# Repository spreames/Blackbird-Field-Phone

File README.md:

# Blackbird Field Phone

A cave rescue field phone for replacing the TP-6N.

#### **Status: Incomplete -- do not for design use until all files loaded**

### Background:

In the USA, cave rescue communications have been done with military field phones for decades. These are two-wire systems that are part of a party-line system (aka parallel connected). The National Cave Rescue Commission (NCRC) has a cache of these phones that are used for training. These units are available in the military surplus stores and online such as eBay. Over the years these field phones have become standard for all cave rescue teams in the USA.

There are three standard field phones that are in use today. The TA-1 ("sound powered" phone) which does not requires batteries but has a very limited range of 2 miles or less. The TA-312 (the "crank phone") has a theoretical range of 20 miles but weights 10.0 lbs with batteries! The TP-6N (the "NATO phone") has the same range but has solid-state circuitry, is much lighter (2.5 lbs), and much smaller.

The problem is that the units are failing. There a no replacement parts, no schematics, and no theory of operation. The most recent model, the TP-6N, was designed in 1973 -- a 50-year old design!

### Introduction to the Blackbird:

In December 2021, the NCRC formed the Communication Committee (CommComm) to address the increasing failure rate with the military phones in the field. The group decided to begin the design of a clone of the TP-6N which was named "Blackbird". Many of the original components are obsolete and very hard to obtain such as custom transformers and uni-junction transistors. So the team designed a functional clone such that works the same as the TP-6N but uses the modern techniques such as SMT components, KiCAD schematics and PCB layouts, 3D printing, and LTspice simulations.

The requirements and goals are:

- Backward compatable with the existing field phones

- Lighter, smaller, and requiring less power

- Runs off three AA batteries

- Is the same cost or less as TP-6Ns on eBay (when they are available)

The complete Goals and Requirements document is 13 pages and is linked here:

xxxxxx

### Block Diagram:

xxxx

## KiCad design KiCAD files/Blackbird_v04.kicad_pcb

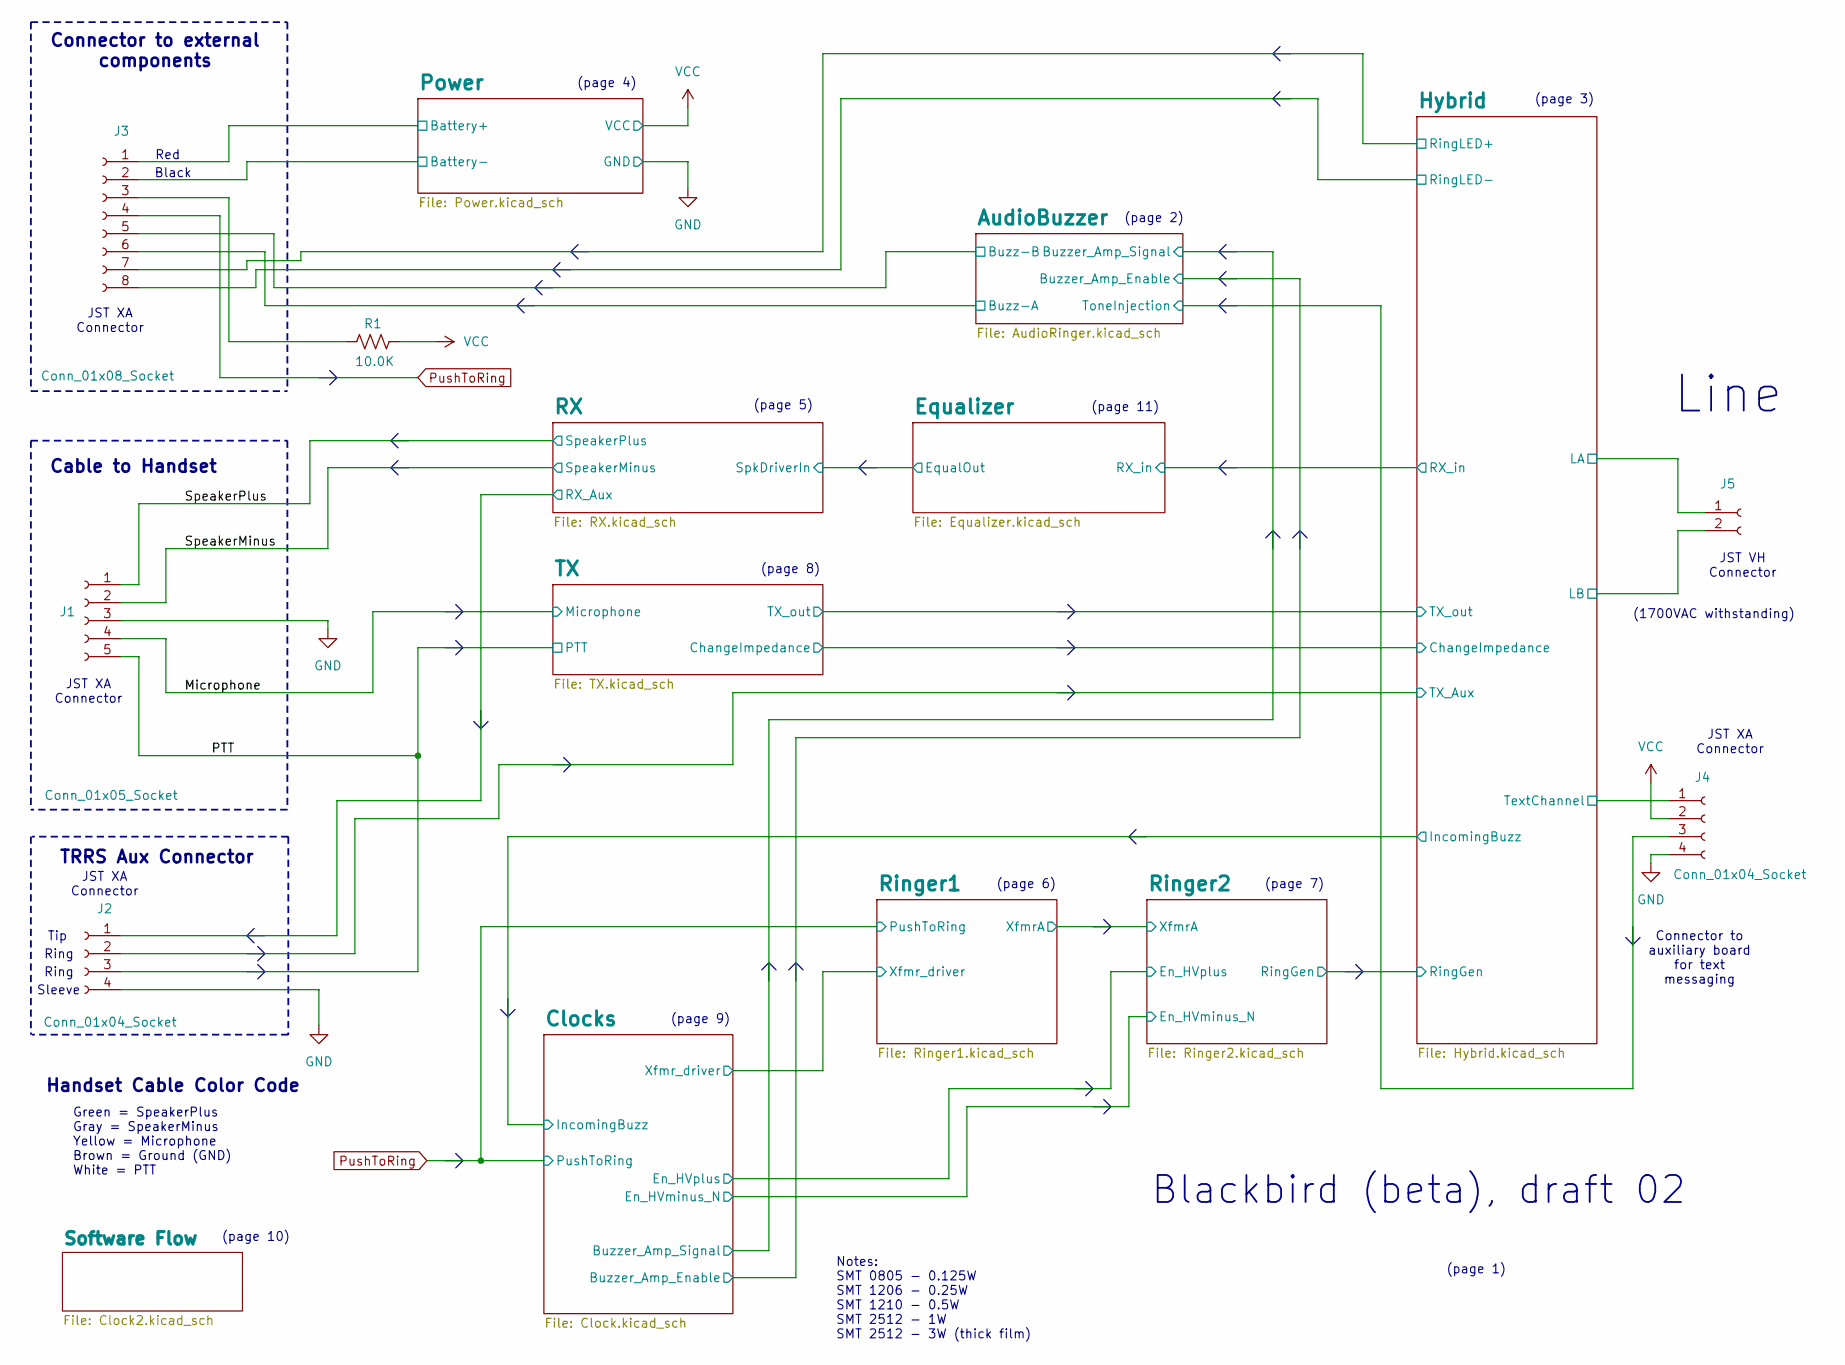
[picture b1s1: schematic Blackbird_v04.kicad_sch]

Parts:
J1: Conn_01x05_Socket; JST_XA_S05B-XASK-1_1x05_P2.50mm_Horizontal_w_housing
J2, J4: Conn_01x04_Socket; JST_XA_S04B-XASK-1_1x04_P2.50mm_Horizontal_w_housing
J3: Conn_01x08_Socket; JST_XA_S08B-XASK-1_1x08_P2.50mm_Horizontal_w_housing
J5: Conn_01x02_Socket; JST_VH_S2P-VH_1x02_P3.96mm_Horizontal_w_housing
R1: 10.0K; R_0805_2012Metric_Pad1.20x1.40mm_HandSolder

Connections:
/AudioBuzzer/Buzz-A: J3.6; also elsewhere on the board
/AudioBuzzer/Buzz-B: J3.5; also elsewhere on the board
/AudioBuzzer/ToneInjection: J4.3; also elsewhere on the board
/Hybrid/LA: J5.1; also elsewhere on the board
/Hybrid/LB: J5.2; also elsewhere on the board
/Hybrid/RingLED+: J3.7; also elsewhere on the board
/Hybrid/RingLED-: J3.8; also elsewhere on the board
/Hybrid/TX_Aux: J2.2; also elsewhere on the board
/Hybrid/TextChannel: J4.1; also elsewhere on the board
/Microphone: J1.4; also elsewhere on the board
/PTT: J1.5, J2.3; also elsewhere on the board
/Power/Battery+: J3.1; also elsewhere on the board
/Power/Battery-: J3.2; also elsewhere on the board
/RX/RX_Aux: J2.1; also elsewhere on the board
/SpeakerMinus: J1.2; also elsewhere on the board
/SpeakerPlus: J1.1; also elsewhere on the board
GND: J1.3, J2.4, J4.4; also elsewhere on the board
unnamed: J3.3, R1.1
PushToRing: J3.4; also elsewhere on the board
VCC: J4.2, R1.2; also elsewhere on the board

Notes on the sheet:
(page 4)
(page 10)
(page 5)
JST XA Connector
(1700VAC withstanding)
Tip
Cable to Handset
Sleeve
JST VH Connector
(page 8)
Green = SpeakerPlus Gray = SpeakerMinus Yellow = Microphone Brown = Ground (GND) White = PTT
(page 7)
Connector to auxiliary board for text messaging
Notes: SMT 0805 - 0.125W SMT 1206 - 0.25W SMT 1210 - 0.5W SMT 2512 - 1W SMT 2512 - 3W (thick film)
(page 11)
(page 9)
(page 1)
Ring
Red
TRRS Aux Connector
Black
(page 2)
Handset Cable Color Code
Connector to external components
(page 3)
Line
(page 6)
Blackbird (beta), draft 02

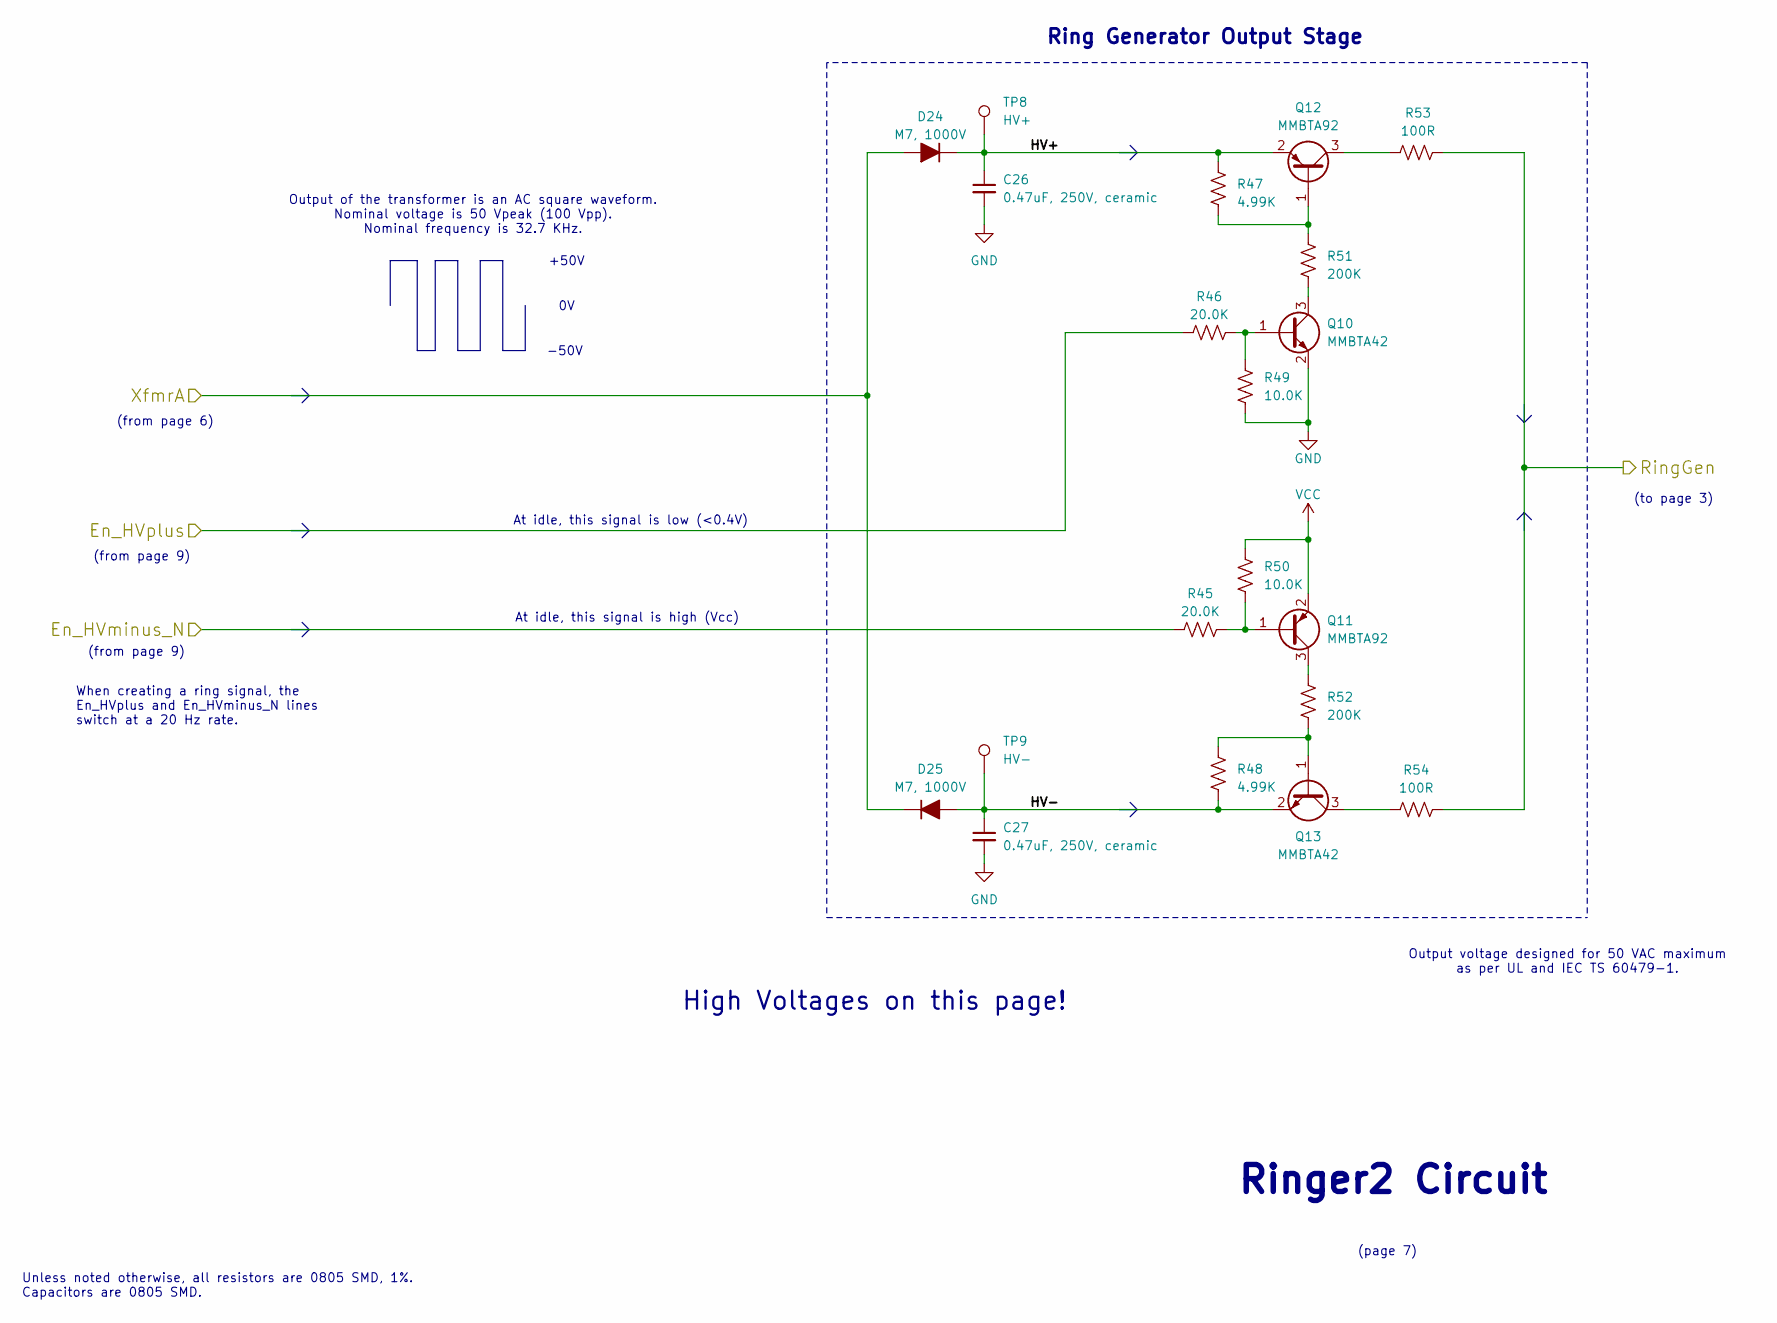
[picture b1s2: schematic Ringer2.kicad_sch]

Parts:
C26, C27: 0.47uF, 250V, ceramic; C_1812_4532Metric_Pad1.57x3.40mm_HandSolder
D24, D25: M7, 1000V; D_SMA_Handsoldering
Q10, Q13: MMBTA42; SOT-23_Handsoldering
Q11, Q12: MMBTA92; SOT-23_Handsoldering
R45, R46: 20.0K; R_0805_2012Metric_Pad1.20x1.40mm_HandSolder
R47, R48: 4.99K; R_0805_2012Metric_Pad1.20x1.40mm_HandSolder
R49, R50: 10.0K; R_0805_2012Metric_Pad1.20x1.40mm_HandSolder
R51, R52: 200K; R_0805_2012Metric_Pad1.20x1.40mm_HandSolder
R53, R54: 100R; R_1210_3225Metric_Pad1.30x2.65mm_HandSolder
TP8: HV+; Test_point_47mil_scope_probe
TP9: HV-; Test_point_47mil_scope_probe

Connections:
/Clocks/En_HVminus_N: R45.1; also elsewhere on the board
/Clocks/En_HVplus: R46.1; also elsewhere on the board
/Hybrid/RingGen: R53.2, R54.2; also elsewhere on the board
/Ringer1/XfmrA: D24.2 (A), D25.1 (K); also elsewhere on the board
/Ringer2/HV+: C26.1, D24.1 (K), Q12.2 (E), R47.1, TP8.1
/Ringer2/HV-: C27.1, D25.2 (A), Q13.2 (E), R48.2, TP9.1
GND: C26.2, C27.2, Q10.2 (E), R49.1; also elsewhere on the board
unnamed: Q10.1 (B), R46.2, R49.2
unnamed: Q10.3 (C), R51.2
unnamed: Q11.1 (B), R45.2, R50.1
unnamed: Q11.3 (C), R52.1
unnamed: Q12.1 (B), R47.2, R51.1
unnamed: Q12.3 (C), R53.1
unnamed: Q13.1 (B), R48.1, R52.2
unnamed: Q13.3 (C), R54.1
VCC: Q11.2 (E), R50.2; also elsewhere on the board

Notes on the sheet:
At idle, this signal is high (Vcc)
When creating a ring signal, the En_HVplus and En_HVminus_N lines switch at a 20 Hz rate.
(from page 6)
Ringer2 Circuit
(from page 9)
(to page 3)
Output of the transformer is an AC square waveform. Nominal voltage is 50 Vpeak (100 Vpp). Nominal frequency is 32.7 KHz.
Output voltage designed for 50 VAC maximum as per UL and IEC TS 60479-1.
Unless noted otherwise, all resistors are 0805 SMD, 1%. Capacitors are 0805 SMD.
+50V
-50V
Ring Generator Output Stage
At idle, this signal is low (<0.4V)
High Voltages on this page!
(page 7)

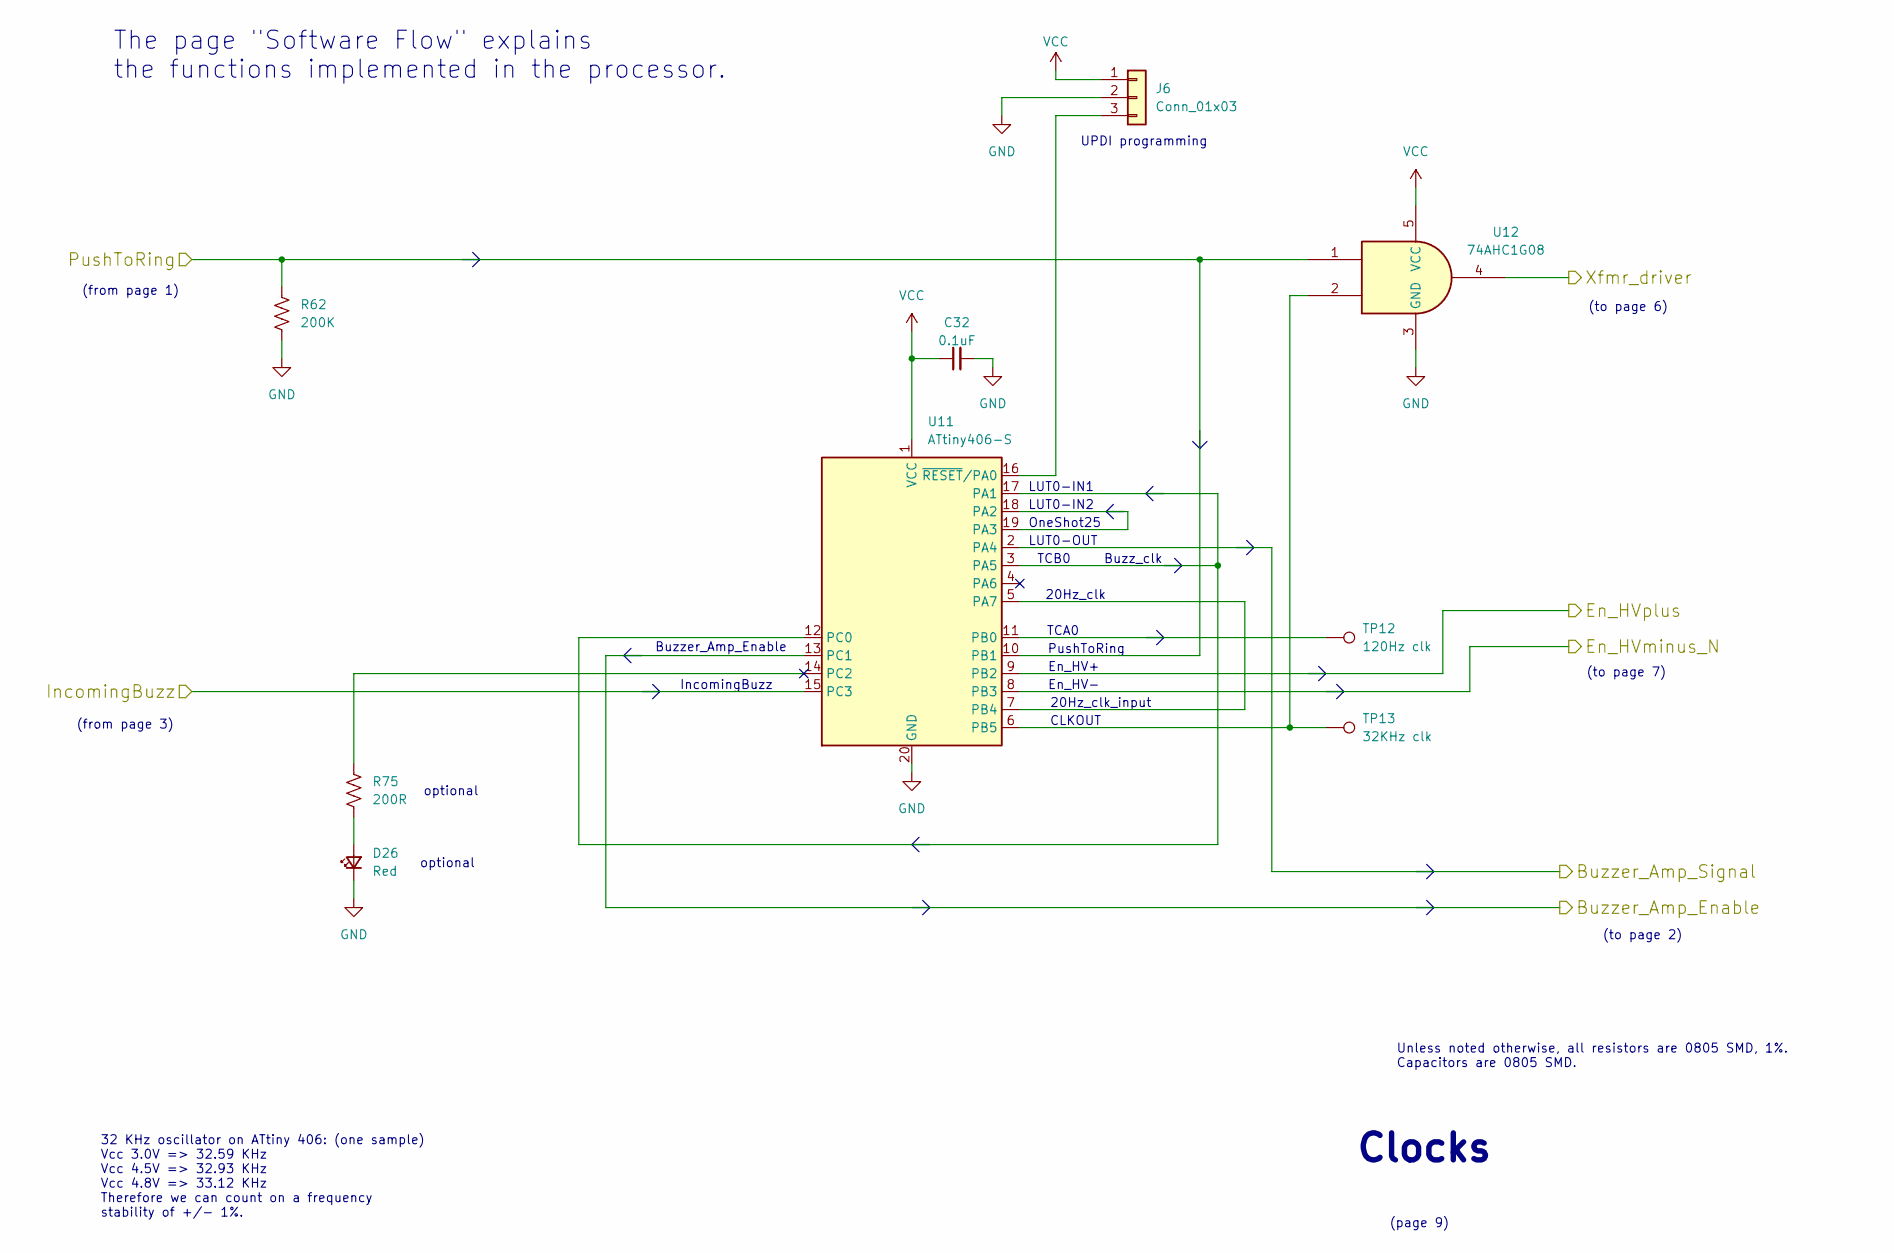
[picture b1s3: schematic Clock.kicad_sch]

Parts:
C32: 0.1uF; C_0805_2012Metric_Pad1.18x1.45mm_HandSolder
D26: Red; LED_1206_3216Metric_Red
J6: Conn_01x03; PinSocket_1x03_P2.54mm_Vertical
R62: 200K; R_0805_2012Metric_Pad1.20x1.40mm_HandSolder
R75: 200R; R_0805_2012Metric_Pad1.20x1.40mm_HandSolder
TP12: 120Hz clk; Test_point_47mil_scope_probe
TP13: 32KHz clk; Test_point_47mil_scope_probe
U11: ATtiny406-S; SOIC-20W_7.5x12.8mm_P1.27mm
U12: 74AHC1G08; SOT-23-5_HandSoldering

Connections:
/AudioBuzzer/Buzzer_Amp_Enable: U11.13 (PC1); also elsewhere on the board
/AudioBuzzer/Buzzer_Amp_Signal: U11.2 (PA4); also elsewhere on the board
/Clocks/En_HVminus_N: U11.8 (PB3); also elsewhere on the board
/Clocks/En_HVplus: U11.9 (PB2); also elsewhere on the board
/Clocks/IncomingBuzz: U11.15 (PC3); also elsewhere on the board
/Clocks/Xfmr_driver: U12.4; also elsewhere on the board
GND: C32.2, D26.1 (K), J6.2, R62.1, U11.20 (GND), U12.3 (GND); also elsewhere on the board
unnamed: D26.2 (A), R75.1
unnamed: J6.3, U11.16 (~RESET/PA0)
unnamed: U11.3 (PA5), U11.12 (PC0), U11.17 (PA1)
unnamed: U11.18 (PA2), U11.19 (PA3)
unnamed: U11.5 (PA7), U11.7 (PB4)
unnamed: TP12.1, U11.11 (PB0)
unnamed: TP13.1, U11.6 (PB5), U12.2
PushToRing: R62.2, U11.10 (PB1), U12.1; also elsewhere on the board
VCC: C32.1, J6.1, U11.1 (VCC), U12.5 (VCC); also elsewhere on the board

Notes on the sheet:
The page "Software Flow" explains the functions implemented in the processor.
LUT0-OUT
Clocks
Buzzer_Amp_Enable
(from page 1)
TCB0
IncomingBuzz
(page 9)
(to page 6)
LUT0-IN1
UPDI programming
OneShot25
En_HV+
20Hz_clk_input
optional
CLKOUT
(to page 2)
Unless noted otherwise, all resistors are 0805 SMD, 1%. Capacitors are 0805 SMD.
En_HV-
TCA0
LUT0-IN2
20Hz_clk
(from page 3)
PushToRing
32 KHz oscillator on ATtiny 406: (one sample) Vcc 3.0V => 32.59 KHz Vcc 4.5V => 32.93 KHz Vcc 4.8V => 33.12 KHz Therefore we can count on a frequency stability of +/- 1%.
(to page 7)
Buzz_clk

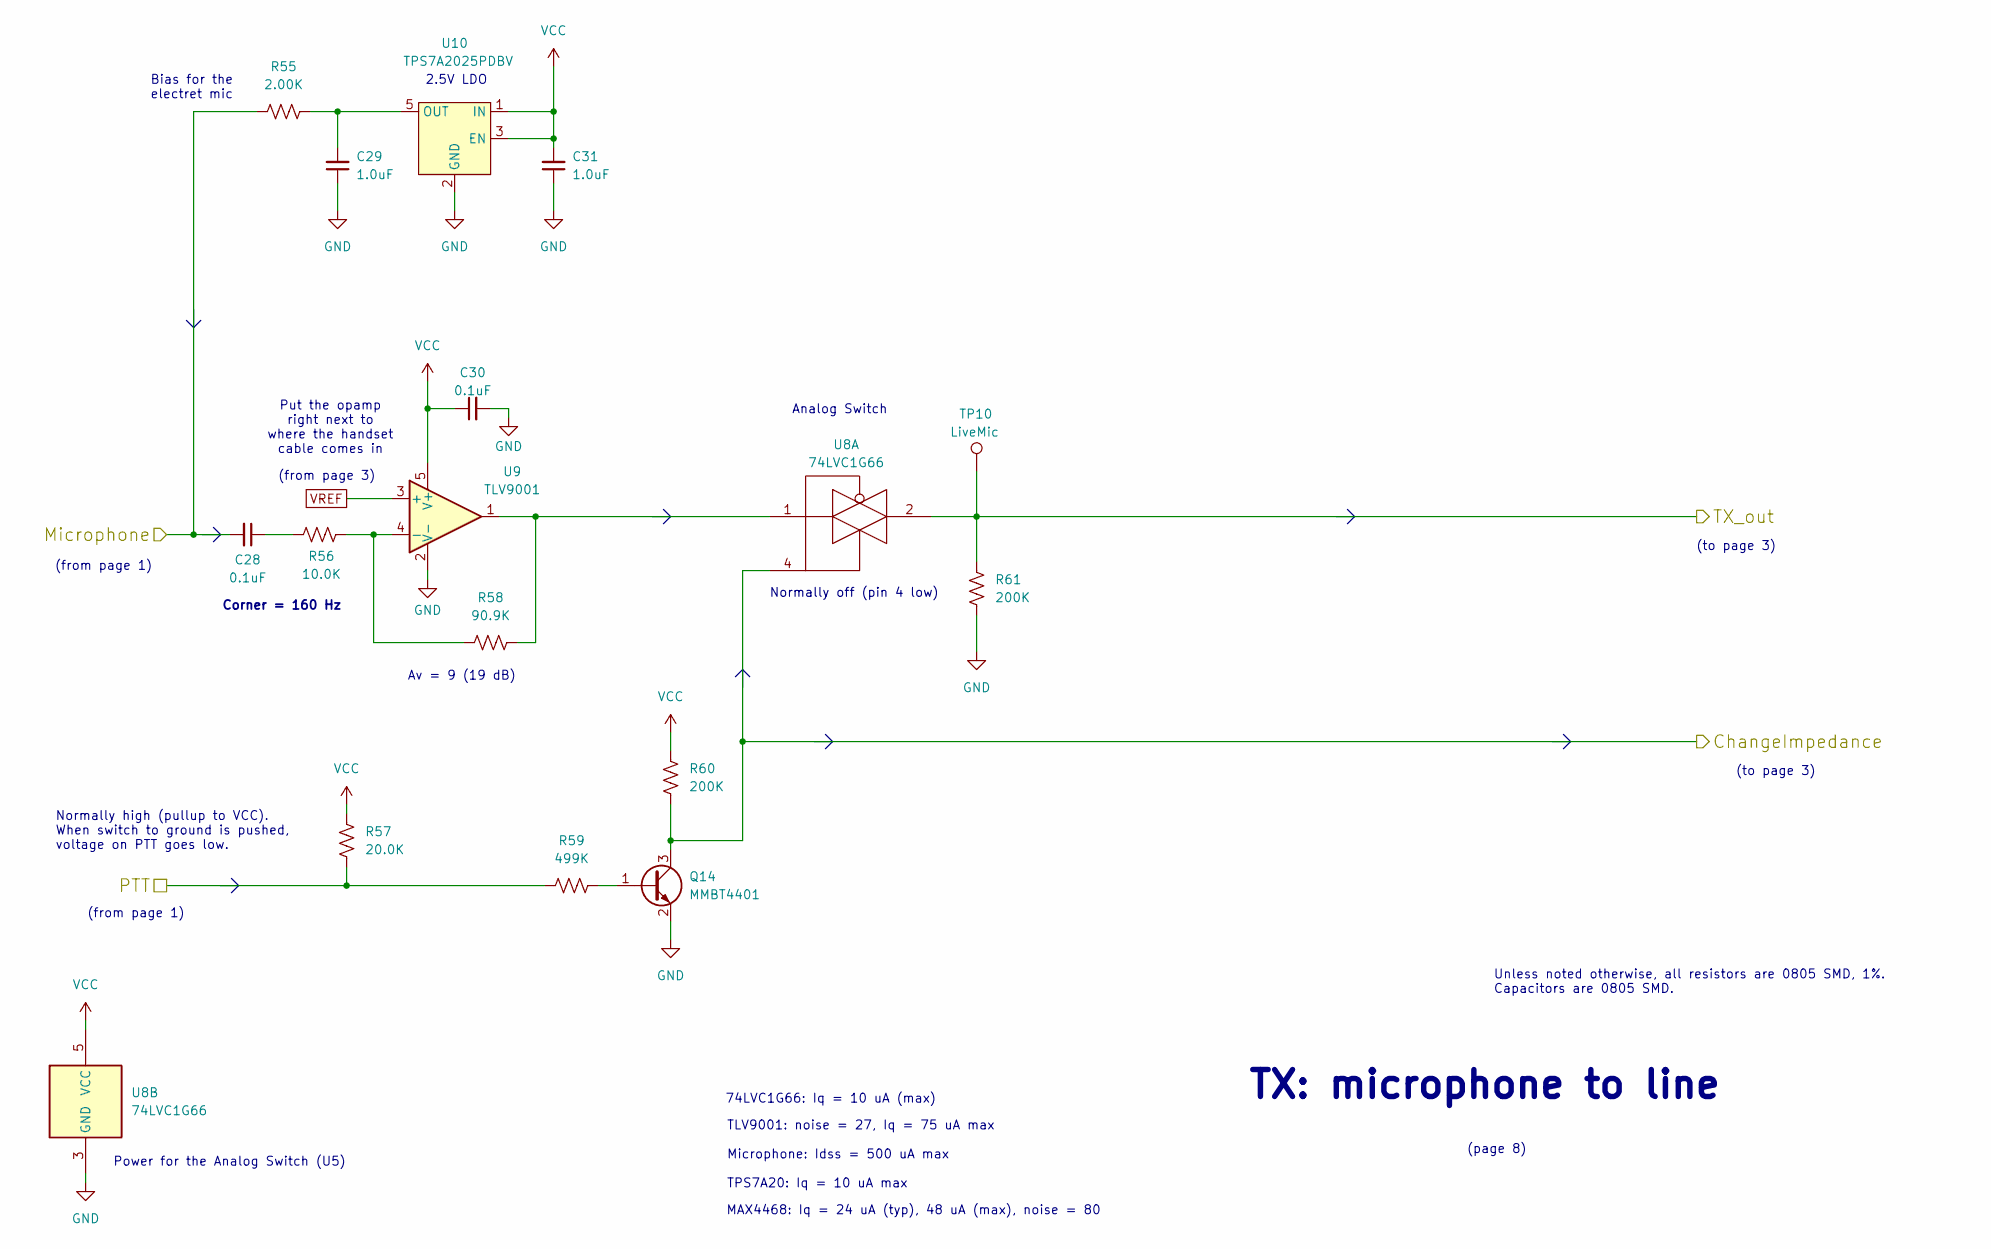
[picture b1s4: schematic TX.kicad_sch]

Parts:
C28, C30: 0.1uF; C_0805_2012Metric_Pad1.18x1.45mm_HandSolder
C29, C31: 1.0uF; C_0805_2012Metric_Pad1.18x1.45mm_HandSolder
Q14: MMBT4401; SOT-23_Handsoldering
R55: 2.00K; R_0805_2012Metric_Pad1.20x1.40mm_HandSolder
R56: 10.0K; R_0805_2012Metric_Pad1.20x1.40mm_HandSolder
R57: 20.0K; R_0805_2012Metric_Pad1.20x1.40mm_HandSolder
R58: 90.9K; R_0805_2012Metric_Pad1.20x1.40mm_HandSolder
R59: 499K; R_0805_2012Metric_Pad1.20x1.40mm_HandSolder
R60, R61: 200K; R_0805_2012Metric_Pad1.20x1.40mm_HandSolder
TP10: LiveMic; Test_point_47mil_scope_probe
U8: 74LVC1G66; SOT-23-5_HandSoldering
U9: TLV9001; SOT-23-5_HandSoldering
U10: TPS7A2025PDBV; SOT-23-5_HandSoldering

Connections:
/Hybrid/ChangeImpedance: Q14.3 (C), R60.1, U8.4; also elsewhere on the board
/Hybrid/TX_out: R61.1, TP10.1, U8.2; also elsewhere on the board
/Microphone: C28.2, R55.1; also elsewhere on the board
/PTT: R57.2, R59.1; also elsewhere on the board
GND: C29.1, C30.2, C31.1, Q14.2 (E), R61.2, U8.3 (GND), U9.2 (V-), U10.2 (GND); also elsewhere on the board
unnamed: C28.1, R56.1
unnamed: Q14.1 (B), R59.2
unnamed: R58.2, U8.1, U9.1
unnamed: R56.2, R58.1, U9.4 (-)
unnamed: C29.2, R55.2, U10.5 (OUT)
VCC: C30.1, C31.2, R57.1, R60.2, U8.5 (VCC), U9.5 (V+), U10.1 (IN), U10.3 (EN); also elsewhere on the board
VREF: U9.3 (+); also elsewhere on the board

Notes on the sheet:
Corner = 160 Hz
TLV9001: noise = 27, Iq = 75 uA max Microphone: Idss = 500 uA max TPS7A20: Iq = 10 uA max
(page 8)
(from page 1)
2.5V LDO
Av = 9 (19 dB)
Unless noted otherwise, all resistors are 0805 SMD, 1%. Capacitors are 0805 SMD.
Normally off (pin 4 low)
TX: microphone to line
Normally high (pullup to VCC). When switch to ground is pushed, voltage on PTT goes low.
Power for the Analog Switch (U5)
Analog Switch
(to page 3)
74LVC1G66: Iq = 10 uA (max)
(from page 3)
Bias for the electret mic
MAX4468: Iq = 24 uA (typ), 48 uA (max), noise = 80
Put the opamp right next to where the handset cable comes in

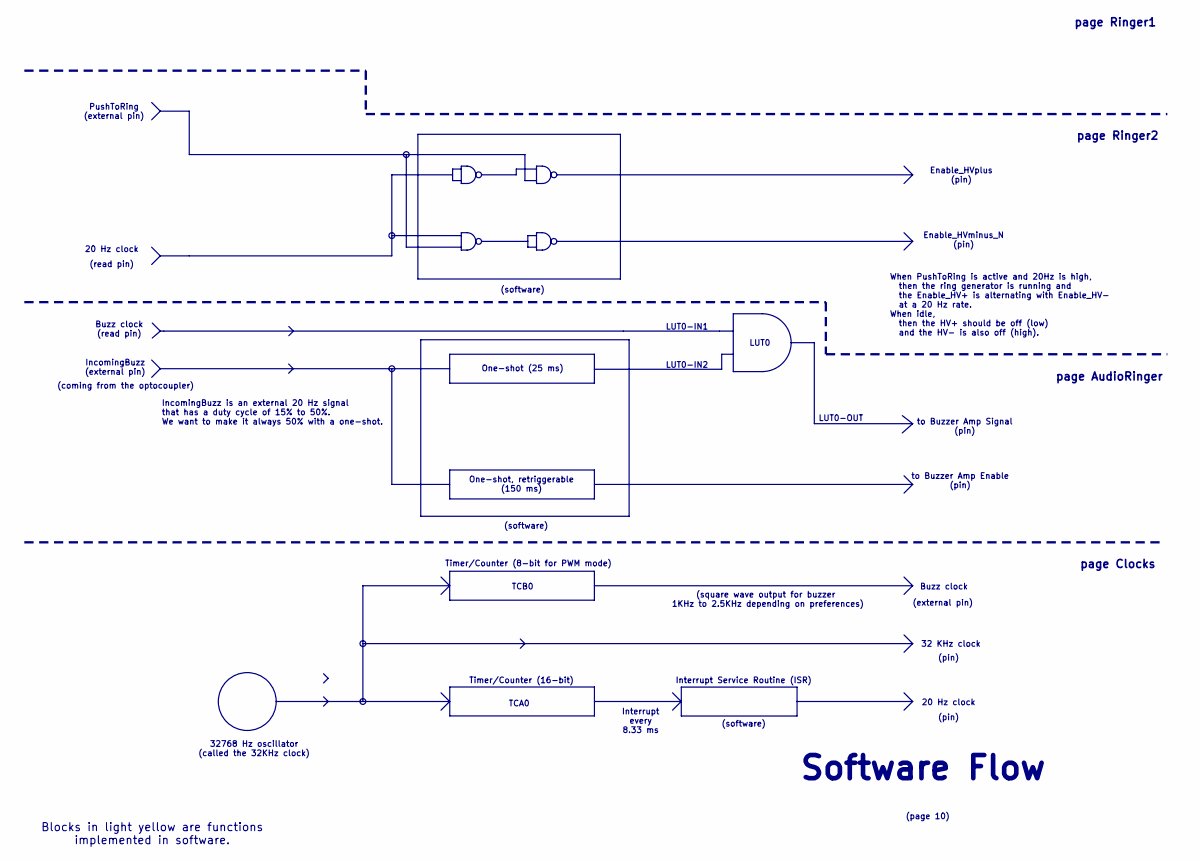
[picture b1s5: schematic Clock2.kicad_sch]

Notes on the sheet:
20 Hz clock
One-shot, retriggerable (150 ms)
Enable_HVminus_N (pin)
32 KHz clock
to Buzzer Amp Signal (pin)
Interrupt Service Routine (ISR)
Timer/Counter (8-bit for PWM mode)
(external pin)
(page 10)
LUT0-IN2
(pin)
Timer/Counter (16-bit)
Blocks in light yellow are functions implemented in software.
page Clocks
Enable_HVplus (pin)
(square wave output for buzzer 1KHz to 2.5KHz depending on preferences)
(software)
Software Flow
page Ringer1
32768 Hz oscillator (called the 32KHz clock)
LUT0-IN1
IncomingBuzz (external pin)
(read pin)
One-shot (25 ms)
PushToRing (external pin)
page AudioRinger
TCA0
page Ringer2
(coming from the optocoupler)
LUT0
IncomingBuzz is an external 20 Hz signal that has a duty cycle of 15% to 50%. We want to make it always 50% with a one-shot.
TCB0
LUT0-OUT
to Buzzer Amp Enable (pin)
Interrupt every 8.33 ms
Buzz clock (read pin)
When PushToRing is active and 20Hz is high, then the ring generator is running and the Enable_HV+ is alternating with Enable_HV- at a 20 Hz rate. When idle, then the HV+ should be off (low) and the HV- is also off (high).
Buzz clock

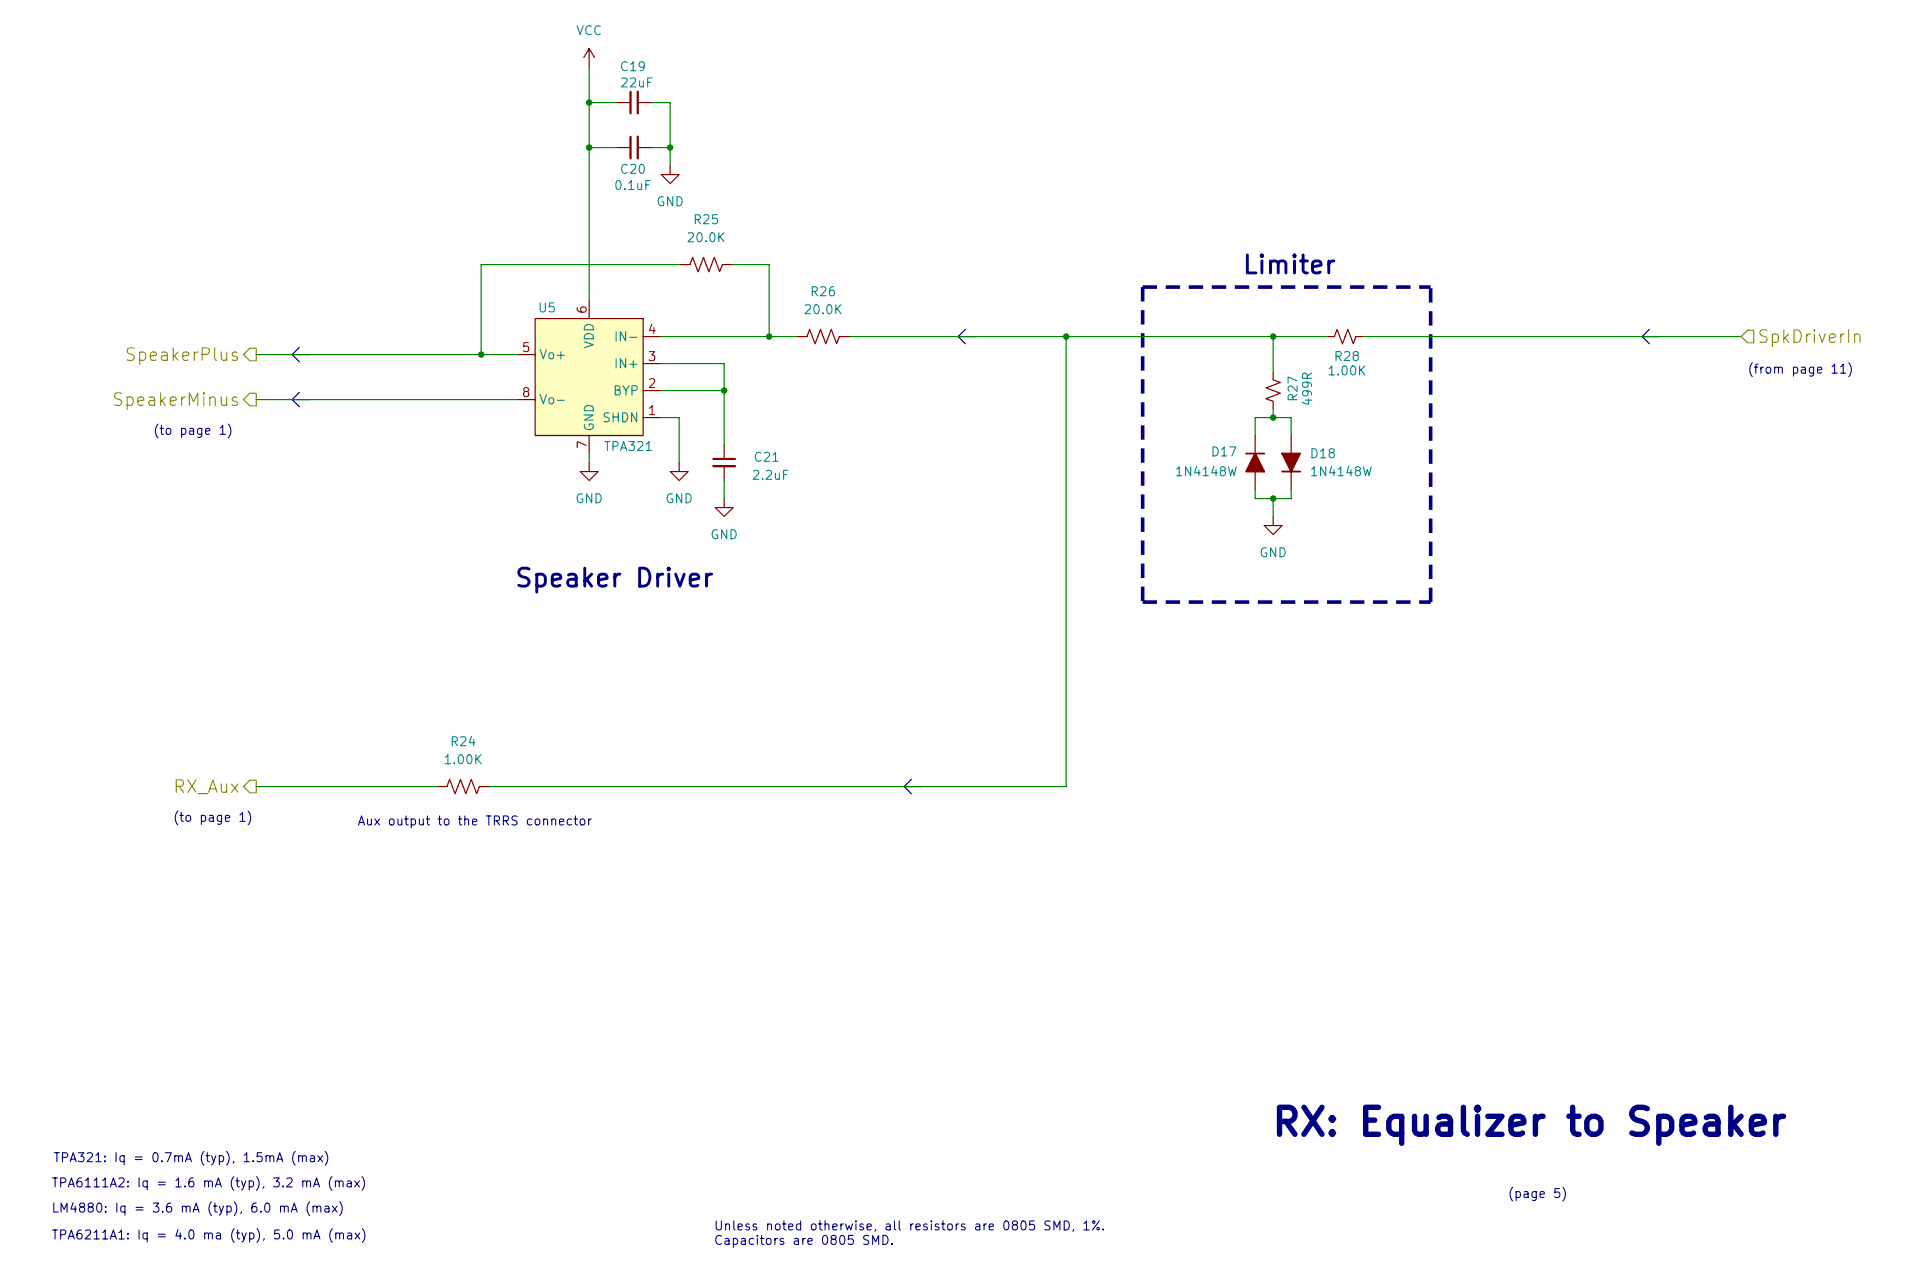
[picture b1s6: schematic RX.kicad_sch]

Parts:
C19: 22uF; C_0805_2012Metric_Pad1.18x1.45mm_HandSolder
C20: 0.1uF; C_0805_2012Metric_Pad1.18x1.45mm_HandSolder
C21: 2.2uF; C_0805_2012Metric_Pad1.18x1.45mm_HandSolder
D17, D18: 1N4148W; D_SOD-123
R24, R28: 1.00K; R_0805_2012Metric_Pad1.20x1.40mm_HandSolder
R25, R26: 20.0K; R_0805_2012Metric_Pad1.20x1.40mm_HandSolder
R27: 499R; R_0805_2012Metric_Pad1.20x1.40mm_HandSolder
U5: TPA321; SOIC-8_3.9x4.9mm_P1.27mm

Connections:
/Equalizer/EqualOut: R28.2; also elsewhere on the board
/RX/RX_Aux: R24.2; also elsewhere on the board
/SpeakerMinus: U5.8 (Vo-); also elsewhere on the board
/SpeakerPlus: R25.2, U5.5 (Vo+); also elsewhere on the board
GND: C19.2, C20.2, C21.2, D17.2 (A), D18.1 (K), U5.1 (SHDN), U5.7 (GND); also elsewhere on the board
unnamed: D17.1 (K), D18.2 (A), R27.1
unnamed: R24.1, R26.1, R27.2, R28.1
unnamed: C21.1, U5.2 (BYP), U5.3 (IN+)
unnamed: R25.1, R26.2, U5.4 (IN-)
VCC: C19.1, C20.1, U5.6 (VDD); also elsewhere on the board

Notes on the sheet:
RX: Equalizer to Speaker
(to page 1)
(from page 11)
Aux output to the TRRS connector
LM4880: Iq = 3.6 mA (typ), 6.0 mA (max)
Speaker Driver
TPA6211A1: Iq = 4.0 ma (typ), 5.0 mA (max)
TPA321: Iq = 0.7mA (typ), 1.5mA (max)
Unless noted otherwise, all resistors are 0805 SMD, 1%. Capacitors are 0805 SMD.
TPA6111A2: Iq = 1.6 mA (typ), 3.2 mA (max)
Limiter
(page 5)
